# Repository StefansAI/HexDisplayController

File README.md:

<h1 style="text-align: center;">HexDisplayController</h1>
<h2 style="text-align: center;">A hexadecimal display module for TTL designs</h2>
<br>
<div style="text-align: center;">
  
</div>
<br>
This small PCB reads an 8-bit input and converts the binary code to a 2 digit 7-segment LED as hexadecimals and 8 single bit LEDs. An input register can capture and hold the input data.
<br><br>
<div style="text-align: center;">
  
</div>
<br>
The processor had been programmed on an Arduino Uno R3 board and then plugged into this controller. 
<br><br>
<div style="text-align: center;">
  
</div>
<br>
The schematic and layout are design in KiCad 9 and the design files are included in the repository.
<br><br>
<div style="text-align: center;">
  
</div>
<br>
<br><br>
The PCB had been made at <a href="www.PCBway.com">PCBway.</a>

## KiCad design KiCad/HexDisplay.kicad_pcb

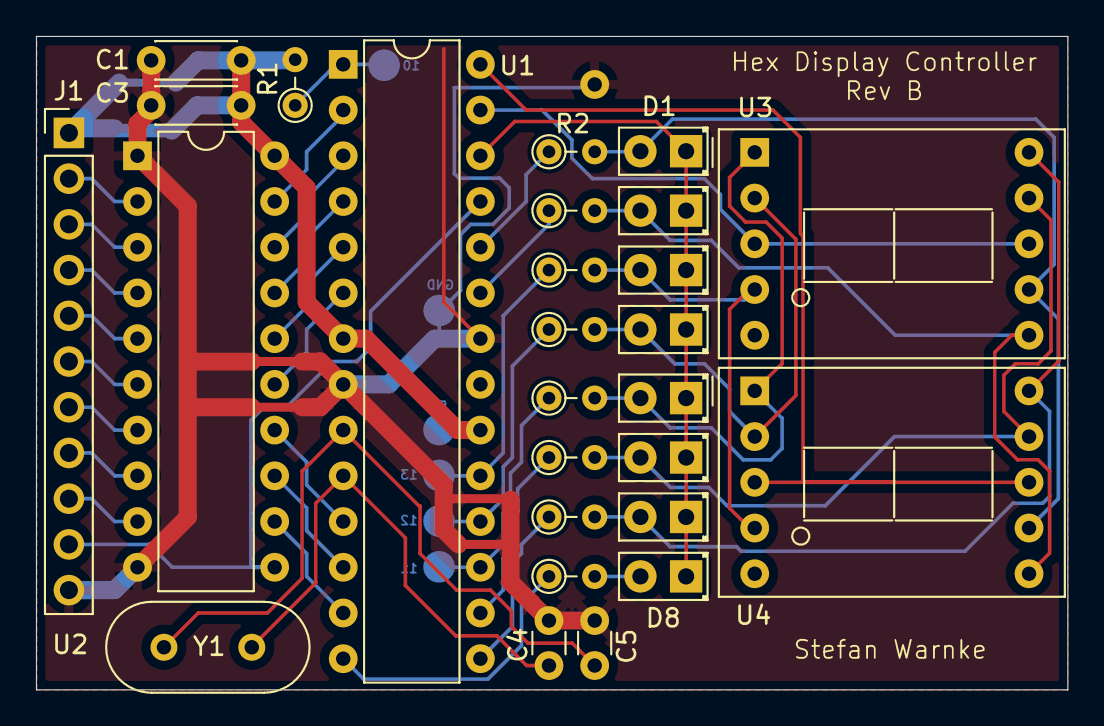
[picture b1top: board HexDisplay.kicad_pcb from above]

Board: 2 copper layers, 57.3 x 36.3 mm, 27 parts (0 on the bottom side), 41 nets.

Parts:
C1: 100n; C_Disc_D4.3mm_W1.9mm_P5.00mm
C3: 4.7u; C_Disc_D4.3mm_W1.9mm_P5.00mm
C4, C5: 22p; C_Disc_D3.0mm_W1.6mm_P2.50mm
D1, D8: LED; LED_D2.0mm_W4.8mm_H2.5mm_FlatTop
D2, D3, D4, D5, D6, D7: LED_D2.0mm_W4.8mm_H2.5mm_FlatTop
J1: Data_In; PinHeader_1x11_P2.54mm_Vertical
R1: 1k; R_Axial_DIN0204_L3.6mm_D1.6mm_P2.54mm_Vertical
R2, R3, R4, R5, R6, R7, R8, R9: 330; R_Axial_DIN0204_L3.6mm_D1.6mm_P2.54mm_Vertical
U1: ATmega328-P; DIP-28_W7.62mm
U2: 74HCT574; DIP-20_W7.62mm
U3, U4: D148K; D1X8K
Y1: 16MHz; Crystal_HC49-U_Vertical

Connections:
+5V: C1.2, C3.1, J1.1, R1.2, U1.7 (VCC), U1.20 (AVCC), U2.20 (VCC)
/D0: R2.1, U1.24 (PC1)
/D1: R3.1, U1.23 (PC0)
/D2: R4.1, U1.19 (PB5)
/D3: R5.1, U1.18 (PB4)
/D4: R6.1, U1.17 (PB3)
/D5: R7.1, U1.16 (PB2)
/D6: R8.1, U1.15 (PB1)
/D7: R9.1, U1.14 (PB0)
/RES: R1.1, U1.1 (~RESET/PC6)
GND: C1.1, C3.2, C4.2, C5.2, J1.11, U1.8 (GND), U1.22 (GND), U2.1 (OE), U2.10 (GND)
unnamed: D1.2 (A), R2.2, U3.7 (A), U4.7 (A)
unnamed: D1.1 (K), D2.1 (K), D3.1 (K), D4.1 (K), D5.1 (K), D6.1 (K), D7.1 (K), D8.1 (K), U1.26 (PC3)
unnamed: D2.2 (A), R3.2, U3.6 (B), U4.6 (B)
unnamed: D3.2 (A), R4.2, U3.4 (C), U4.4 (C)
unnamed: D4.2 (A), R5.2, U3.2 (D), U4.2 (D)
unnamed: D5.2 (A), R6.2, U3.1 (E), U4.1 (E)
unnamed: D6.2 (A), R7.2, U3.9 (F), U4.9 (F)
unnamed: D7.2 (A), R8.2, U3.10 (G), U4.10 (G)
unnamed: D8.2 (A), R9.2
unnamed: J1.2, U2.2 (D0)
unnamed: J1.3, U2.3 (D1)
unnamed: J1.4, U2.4 (D2)
unnamed: J1.5, U2.5 (D3)
unnamed: J1.6, U2.6 (D4)
unnamed: J1.7, U2.7 (D5)
unnamed: J1.8, U2.8 (D6)
unnamed: J1.9, U2.9 (D7)
unnamed: J1.10, U1.25 (PC2), U2.11 (Cp)
unnamed: U1.27 (PC4), U3.3 (CC), U3.8 (CC)
unnamed: U1.28 (PC5), U4.3 (CC), U4.8 (CC)
unnamed: U1.2 (PD0), U2.19 (Q0)
unnamed: U1.3 (PD1), U2.18 (Q1)
unnamed: U1.4 (PD2), U2.17 (Q2)
unnamed: U1.5 (PD3), U2.16 (Q3)
unnamed: U1.6 (PD4), U2.15 (Q4)
unnamed: U1.11 (PD5), U2.14 (Q5)
unnamed: U1.12 (PD6), U2.13 (Q6)
unnamed: U1.13 (PD7), U2.12 (Q7)
unnamed: C5.1, U1.9 (XTAL1/PB6), Y1.2
unnamed: C4.1, U1.10 (XTAL2/PB7), Y1.1

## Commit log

2025-09-09 Initial Check-in
2025-09-10 Update and README.md
    README documentation added
2025-11-15 Updates of KiCad files and README
